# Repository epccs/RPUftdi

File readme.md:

# RPUusb

From <https://github.com/epccs/RPUusb>

## Overview

Alow a desktop or other host with USB to interface with [Gravimetric] that have an R-Pi header. It has two UARTs that can together operate the multi-drop serial. 

[Gravimetric]: https://github.com/epccs/Gravimetric

## Status

This board has a known problem with managers that lack power domains that allow one side to power down, that is to say if it has power and the application does not then the manager on the application board will be damaged. It is my hope that I can figure out how to use one of the new AVR-DB chips as a manager to fix this problem.

This is programmed with an in-circuit serial programming tool that is able to handle the 3.3V ATmega328pb target. I use an Arduino Uno with the [ArduinoISP] sketch and an SPI level shifter.

[ICSP]: https://github.com/epccs/Driver/tree/master/ICSP

[ArduinoISP]: https://github.com/arduino/Arduino/blob/master/build/shared/examples/11.ArduinoISP/ArduinoISP/ArduinoISP.ino

## [Hardware](./Hardware)

Hardware files and notes for referance.

## Example

TBD

## AVR toolchain

The core files for this board are in the /lib folder. Each example has its files and a Makefile in its own folder. The toolchain packages that I use are available on Ubuntu, Raspbian and Windows with WSL and Ubuntu installed. 

```
sudo apt-get install git make gcc-avr binutils-avr gdb-avr avr-libc avrdude
git clone https://github.com/epccs/RPUusb
```

* [gcc-avr](https://packages.ubuntu.com/search?keywords=gcc-avr)
* [binutils-avr](https://packages.ubuntu.com/search?keywords=binutils-avr)
* [gdb-avr](https://packages.ubuntu.com/search?keywords=gdb-avr)
* [avr-libc](https://packages.ubuntu.com/search?keywords=avr-libc)
* [avrdude](https://packages.ubuntu.com/search?keywords=avrdude)

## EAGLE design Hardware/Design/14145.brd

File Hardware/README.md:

# Hardware

## Overview

USB interface that plugs in place of an R-Pi. It plugs into an R-Pi header (e.g., [Gravimetric]). The CP2105 chip has two UARTs. The full-duplex multidrop bus is directly connected to the primary UART, while the secondary UART is connected to an MCU (ATmega328pb) that can act as a bridge for many of the R-Pi header pins (e.g., SPI, I2C) from the target board. A USB host can set the bootload address on the multi-drop serial with the I2C interface from the 328pb, and some other functions that an R-Pi has access to from the manager.

[Gravimetric]: https://github.com/epccs/Gravimetric

## Inputs/Outputs/Functions

* Full Duplex TX and RX from USB serial0 on R-Pi header pin 8 and 10.
* RTS and CTS from USB serial0 on R-Pi header pin 36 and 11.
* USB serial1 connects with an ATmega328pb for use with I2C/SPI.
* Fits RPUpi or Gravimetric.

## Uses

* Plugs in place of an R-Pi to allow USB from a computer to communicate with an RPU target.

# Table Of Contents

1. [Status](#status)
2. [Design](#design)
3. [Bill of Materials](#bill-of-materials)
4. [How To Use](#how-to-use)

# Status

```
        ^5  Done: Design (# = done), Layout, BOM, Review*, Order Boards, Assembly, Testing,
            WIP: Evaluation.
            Todo: 
            *during review the Design may change without changing the revision.
            High risk of damage to manager on application board, if manager has dual power domains that may fix
            # remove arduino headers
            # add header with 40 pin R-Pi pinout
            # swap MCU to ATmega328pb
            # swap ftdi with a dual UART port version Silabs CP2105
            # connect serial0 to RX/TX/nRTS/nCTS on R-Pi header
            # connect sierial1 to MCU's serial0
            # connect MCU's I2C0 to I2C on R-Pi header
            # connect MCU's I2C1 to the ID port on R-Pi header
            # connect MCU's SPI to SPI on R-Pi header
            # power with 3V3 from LDO and power the LDO from the USB header through the P-CH soft start. 

        ^4 Done: Design, Layout, BOM, Review*, Order Boards, Assembly, Testing, Evaluation.
           WIP: 
           Todo:  
           *during review the Design may change without changing the revision.
           location: 2017-3-17 Test Bench /w an OSEPP Uno R3

        ^3 location: 2016-10-1 Test Bench /w an OSEPP Uno R3, used to connect by CAT5 to outside parts and to bench parts as needed.
                     2017-1-5 ICP1 hacked open.
                     2017-3-17 scraped
```

Debugging and fixing problems i.e. [Schooling](./Schooling/)

Setup and methods used for [Evaluation](./Evaluation/)

# Design

The board is 0.063 thick, FR4, two layer, 1 oz copper with ENIG (gold) finish.

## Mounting

```
        Plugs into the R-Pi header of a multi-drop serial board.
```

## Electrical Schematic

## Testing

Check correct assembly and function with [Testing](./Testing/)

# Bill of Materials

The BOM is a CVS file, import it into a spreadsheet program like LibreOffice Calc (or Excel), or use a text editor.

Option | BOM's included
----- | ----- 
A. | [BRD] 
M. | [BRD] [SMD] [HDR] 

[BRD]: ./Design/14145BRD,BOM.csv
[SMD]: ./Design/14145SMD,BOM.csv
[HDR]: ./Design/14145HDR,BOM.csv

[Order Form](https://rpubus.org/Order_Form.html)

# How To Use

TDD

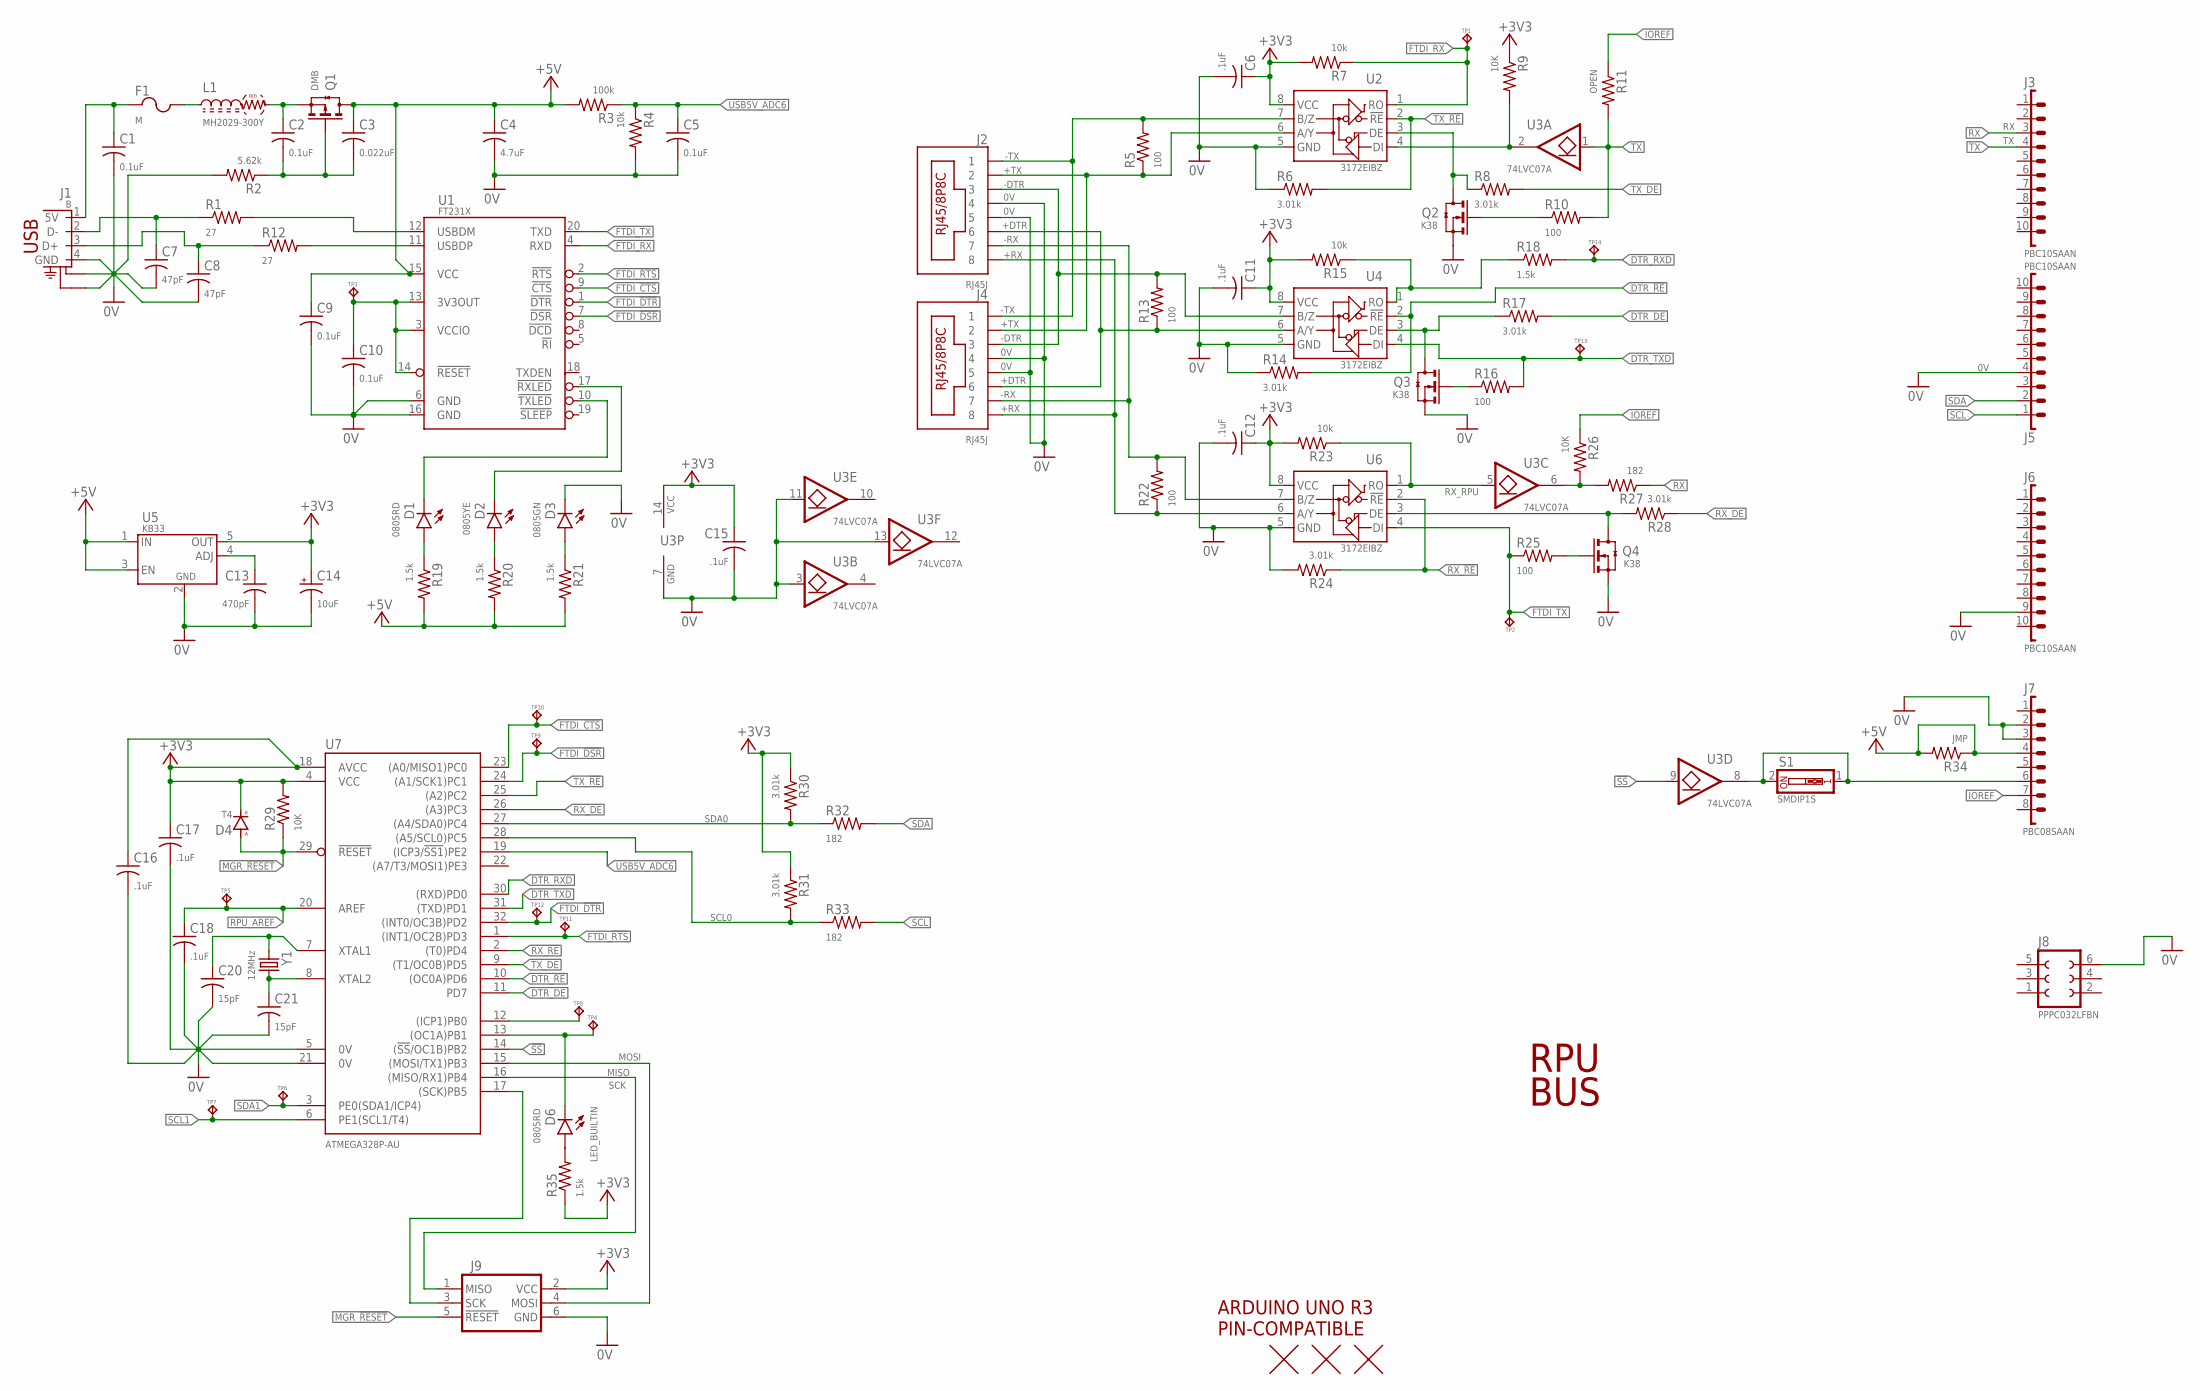
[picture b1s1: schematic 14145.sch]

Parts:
C1, C2, C5, C9, C10: 0.1uF; C0603(1608)
C3: 0.022uF; C0603(1608)
C4: 4.7uF; C1206(3216)
C6, C11, C12, C15, C16, C17, C18: .1uF; C0603(1608)
C7, C8: 47pF; C0603(1608)
C13: 470pF; C0603(1608)
C14: 10uF; 3216
C20, C21: 15pF; C0603(1608)
D1, D6: 0805RD; C0805(2012)
D2: 0805YE; C0805(2012)
D3: 0805GN; C0805(2012)
D4: T4; SOD123
F1: M; C1210(3225)
J1: B; USB-B-PTH
J2, J4: RJ45J; RJ45-8HZT
J3, J5, J6: PBC10SAAN; 1X10
J7: PBC08SAAN; 1X8
J8: PPPC032LFBN; F2X3
J9: ISP-SPIPTH; ISP
L1: MH2029-300Y; C0805(2012)
Q1: DMB; SOT23
Q2, Q3, Q4: K38; SOT23
R1, R12: 27; C0805(2012)
R2: 5.62k; C0805(2012)
R3: 100k; C0805(2012)
R4, R7, R15, R23: 10k; C0805(2012)
R5, R10, R13, R16, R22, R25: 100; C0805(2012)
R6, R8, R14, R17, R24, R28, R30, R31: 3.01k; C0805(2012)
R9, R26, R29: 10K; C0805(2012)
R11: OPEN; C0805(2012)
R18, R19, R20, R21, R35: 1.5k; C0805(2012)
R27, R32, R33: 182; C0805(2012)
R34: JMP; C0805(2012)
S1: SMDIP1S; SMD-DIPSWITCH-1
TP1, TP2, TP3, TP4, TP5, TP6, TP7, TP8, TP9, TP10, TP11, TP12, TP13, TP14: TPPAD1-08; P1-08
U1: FT231X; 20SSOP
U2, U4, U6: 3172EIBZ; SOIC8
U3: 74LVC07A; 14SOIC
U5: KB33; SOT23-5,SOT25
U7: ATMEGA328P-AU; TQFP32-08
U$1: ARDUINO-UNO; ARDUINO_UNO
U$2, U$3, U$4: FIDUCIAL1.27; FIDUCIAL-1.27
Y1: 12MHz; CSM-3X

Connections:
0V: C1.2, C4.2, C5.2, C6.2, C7.2, C8.2, C9.2, C10.2, C11.2, C12.2, C13.2, C14.-, C15.2, C16.2, C17.2, C18.2, C20.2, C21.2, D3.K, J1.4 (GND), J1.S1 (CHASSIS1), J1.S2 (CHASSIS2), J2.4, J2.5, J4.4, J4.5, J5.4, J6.9, J7.2, J7.3, J8.6, J9.6 (GND), Q2.2(S) (S), Q3.2(S) (S), Q4.2(S) (S), R2.2, R4.2, R6.1, R14.1, R24.2, U1.6 (GND), U1.16 (GND), U2.5 (GND), U3.3 (I), U3.7 (GND), U3.11 (I), U3.13 (I), U4.5 (GND), U5.2 (GND), U6.5 (GND), U7.5 (0V), U7.21 (0V)
!SS!: U3.9 (I), U7.14 ((!SS!/OC1B)PB2)
+3V3: C6.1, C11.1, C12.1, C14.+, C15.1, C16.1, C17.1, D4.C (K), J9.2 (VCC), R7.2, R9.1, R15.2, R23.2, R29.2, R30.1, R31.1, R35.1, U2.8 (VCC), U3.14 (VCC), U4.8 (VCC), U5.5 (OUT), U6.8 (VCC), U7.4 (VCC), U7.18 (AVCC)
+5V: C3.1, C4.1, C9.1, J7.4, Q1.3(D) (D), R3.2, R19.2, R20.2, R21.2, R34.1, R34.2, U1.15 (VCC), U5.1 (IN), U5.3 (EN)
+DTR: J2.6, J4.6, R13.1, U4.6 (A/Y)
+RX: J2.8, J4.8, R22.1, U6.6 (A/Y)
+TX: J2.2, J4.2, R5.1, U2.6 (A/Y)
-DTR: J2.3, J4.3, R13.2, U4.7 (B/Z)
-RX: J2.7, J4.7, R22.2, U6.7 (B/Z)
-TX: J2.1, J4.1, R5.2, U2.7 (B/Z)
D+: C8.1, J1.3 (D+), R12.1
D-: C7.1, J1.2 (D-), R1.1
DTR_!RE: R14.2, U4.2 (!RE), U7.10 ((OC0A)PD6)
DTR_DE: R17.2, U7.11 (PD7)
DTR_RXD: R18.2, TP14.TP, U7.30 ((RXD)PD0)
DTR_TXD: R16.2, TP13.TP, U4.4 (DI), U7.31 ((TXD)PD1)
FT3V3: C10.1, TP3.TP, U1.3 (VCCIO), U1.13 (3V3OUT), U1.14 (!RESET!)
FTDI_!CTS: TP10.TP, U1.9 (!CTS!), U7.23 ((A0/MISO1)PC0)
FTDI_!DSR: TP9.TP, U1.7 (!DSR!), U7.24 ((A1/SCK1)PC1)
FTDI_!DTR: TP12.TP, U1.1 (!DTR!), U7.32 ((INT0/OC3B)PD2)
FTDI_!RTS: TP11.TP, U1.2 (!RTS!), U7.1 ((INT1/OC2B)PD3)
FTDI_RX: R7.1, TP1.TP, U1.4 (RXD), U2.1 (RO)
FTDI_TX: R25.1, TP2.TP, U1.20 (TXD), U6.4 (DI)
IOREF: J7.7, R11.1, R26.1
LED_BUILTIN: D6.K, TP4.TP, U7.13 ((OC1A)PB1)
MGR_!RESET: D4.A, J9.5 (!RESET), R29.1, U7.29 (!RESET)
MISO: J9.1 (MISO), U7.16 ((MISO/RX1)PB4)
MOSI: J9.4 (MOSI), U7.15 ((MOSI/TX1)PB3)
unnamed: TP8.TP, U7.12 ((ICP1)PB0)
unnamed: J7.6, S1.1, S1.2, U3.8 (O)
unnamed: C1.1, F1.1, J1.1 (5V)
unnamed: F1.2, L1.1
unnamed: D2.A, R20.1
unnamed: D1.K, U1.10 (!TXLED)
unnamed: D2.K, U1.17 (!RXLED)
unnamed: R26.2, R27.2, U3.6 (O)
unnamed: Q4.3(D) (D), R28.2, U6.3 (DE)
unnamed: R1.2, U1.12 (USBDM)
unnamed: R12.2, U1.11 (USBDP)
unnamed: D3.A, R21.1
unnamed: Q2.1(G) (G), R10.1
unnamed: D1.A, R19.1
unnamed: Q2.3(D) (D), R8.1, U2.3 (DE)
unnamed: R15.1, R18.1, U4.1 (RO)
unnamed: Q3.3(D) (D), R17.1, U4.3 (DE)
unnamed: Q3.1(G) (G), R16.1
unnamed: C13.1, U5.4 (ADJ)
unnamed: Q4.1(G) (G), R25.2
unnamed: C2.1, L1.2, Q1.2(S) (S)
unnamed: C2.2, C3.2, Q1.1(G) (G), R2.1
unnamed: D6.A, R35.2
RPU_AREF: C18.1, TP5.TP, U7.20 (AREF)
RX: J3.3, R27.1
RX_!RE: R24.1, U6.2 (!RE), U7.2 ((T0)PD4)
RX_DE: R28.1, U7.26 ((A3)PC3)
RX_RPU: R23.1, U3.5 (I), U6.1 (RO)
SCK: J9.3 (SCK), U7.17 ((SCK)PB5)
SCL: J5.1, R33.2
SCL0: R31.2, R33.1, U7.28 ((A5/SCL0)PC5)
SCL1: TP7.TP, U7.6 (PE1(SCL1/T4))
SDA: J5.2, R32.2
SDA0: R30.2, R32.1, U7.27 ((A4/SDA0)PC4)
SDA1: TP6.TP, U7.3 (PE0(SDA1/ICP4))
TX: J3.4, R10.2, R11.2, U3.1 (I)
TX_!RE: R6.2, U2.2 (!RE), U7.25 ((A2)PC2)
TX_DE: R8.2, U7.9 ((T1/OC0B)PD5)
TX_RPU: R9.2, U2.4 (DI), U3.2 (O)
USB5V_ADC6: C5.1, R3.1, R4.1, U7.19 ((ICP3/!SS1!)PE2)
XTAL1: C20.1, U7.7 (XTAL1), Y1.1
XTAL2: C21.1, U7.8 (XTAL2), Y1.2

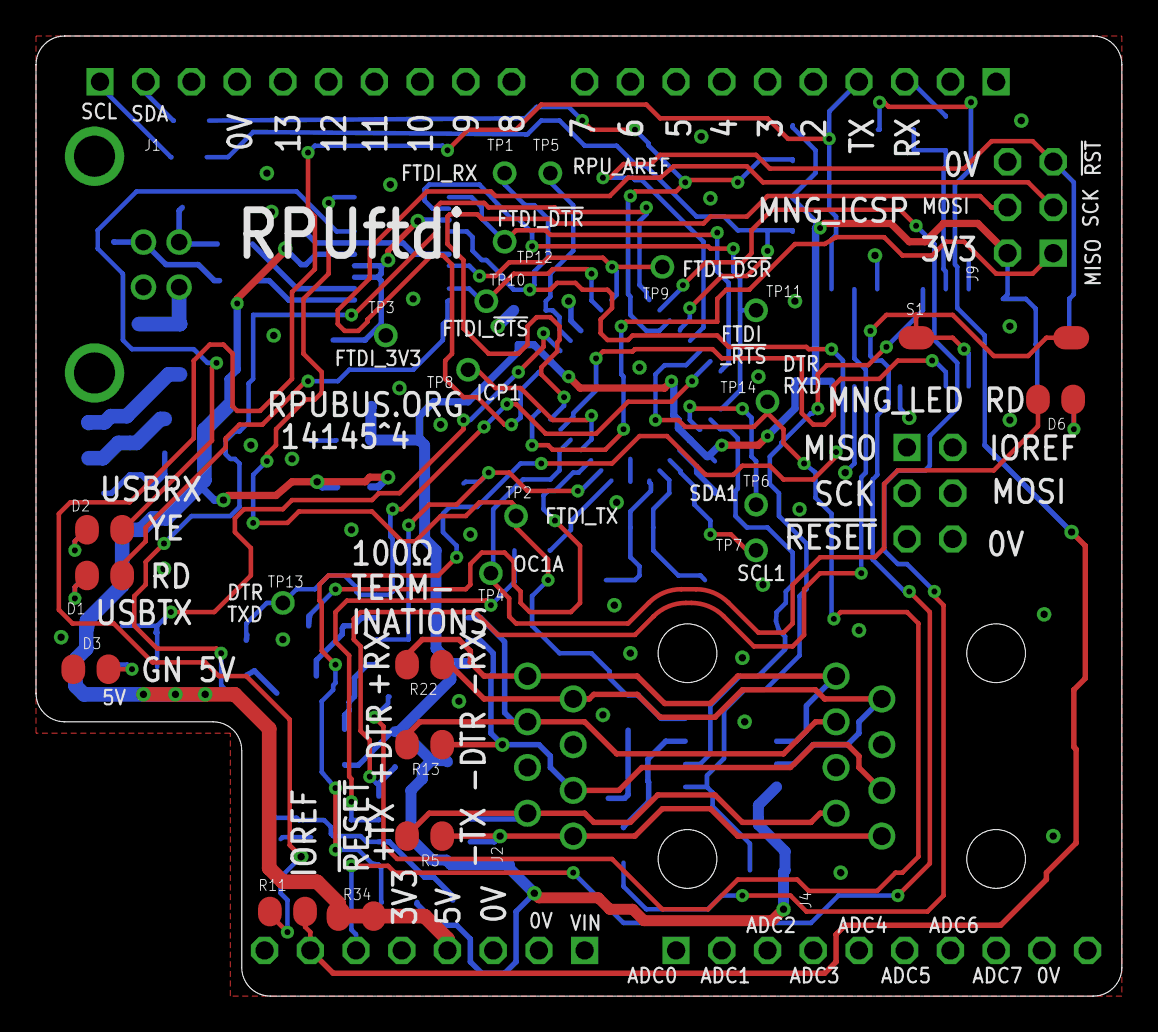
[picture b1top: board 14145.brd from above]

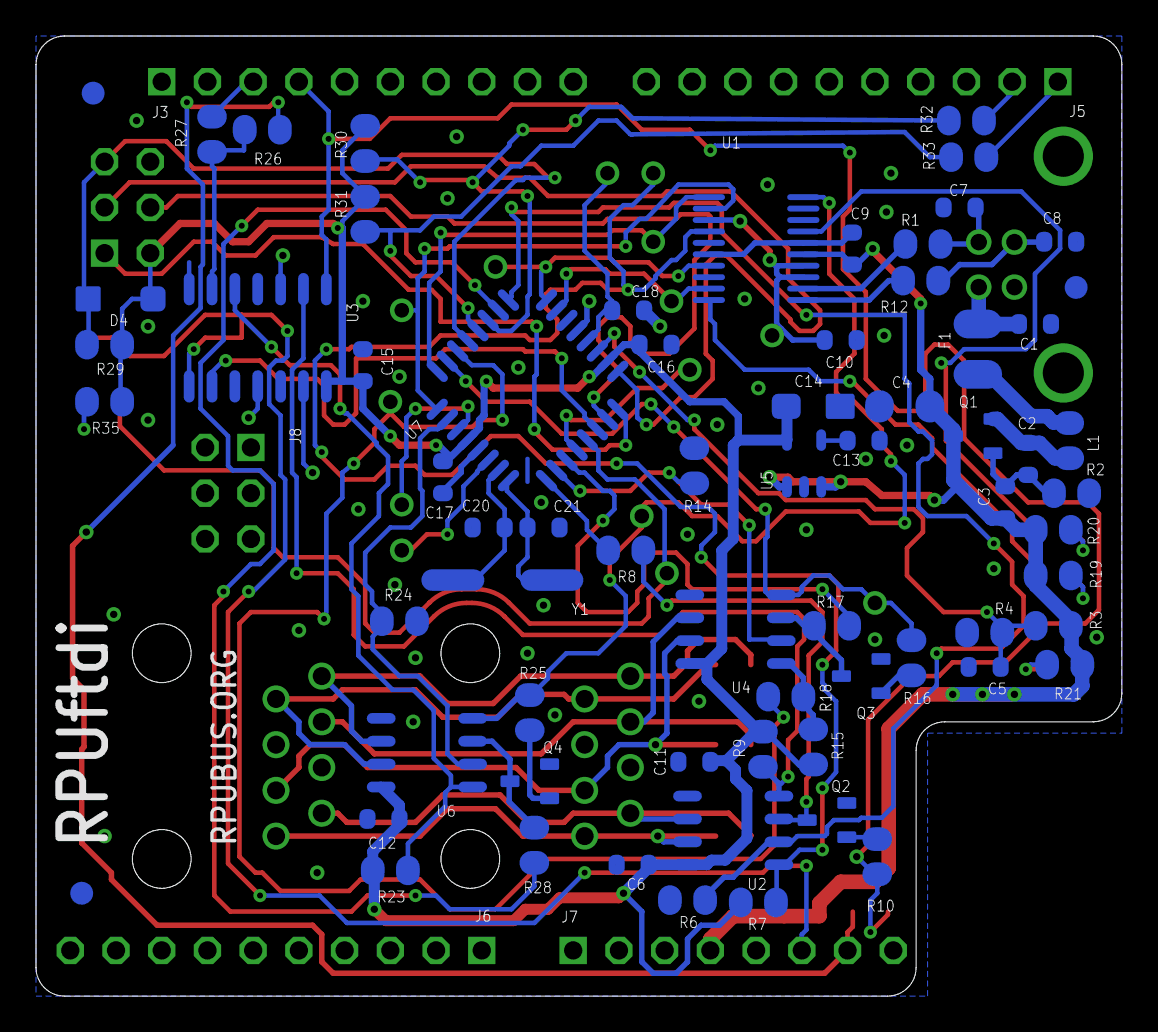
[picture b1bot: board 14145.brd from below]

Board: 2 copper layers, 60.3 x 53.3 mm, 102 parts (73 on the bottom side), 70 nets.

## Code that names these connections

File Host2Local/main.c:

/* Host2Local is for ATMega328 bus manager on RPUftdi board
 This program is free software; you can redistribute it and/or
modify it under the terms of the GNU General Public License
as published by the Free Software Foundation; either version 2
of the License, or (at your option) any later version.

This program is distributed in the hope that it will be useful,
but WITHOUT ANY WARRANTY; without even the implied warranty of
MERCHANTABILITY or FITNESS FOR A PARTICULAR PURPOSE.  See the
GNU General Public License for more details.

For a copy of the GNU General Public License use
http://www.gnu.org/licenses/gpl-2.0.html
 */ 

#include <util/delay.h>
#include <avr/io.h>
#include "../lib/timers.h"
#include "../lib/pin_num.h"
#include "../lib/pins_board.h"

#define BLINK_DELAY 500

static unsigned long blink_started_at;

int main(void)
{
    pinMode(LED_BUILTIN, OUTPUT);
    digitalWrite(LED_BUILTIN, HIGH);
    pinMode(FTDI_nRTS, INPUT);
    pinMode(FTDI_nCTS, OUTPUT);
    digitalWrite(FTDI_nCTS, LOW);
    pinMode(FTDI_nDTR, INPUT);
    pinMode(FTDI_nDSR, OUTPUT);
    digitalWrite(FTDI_nDSR, LOW);
    pinMode(RX_DE, OUTPUT);
    digitalWrite(RX_DE, HIGH); // allow RX pair driver to enable if FTDI_TX is low
    pinMode(TX_DE, OUTPUT);
    digitalWrite(TX_DE, HIGH); // allow TX pair driver to enable if TX (from MCU) is low
    pinMode(DTR_nRE, OUTPUT);
    digitalWrite(DTR_nRE, HIGH); // disable DTR pair receiver
    pinMode(DTR_DE, OUTPUT);
    digitalWrite(DTR_DE, LOW); // disable DTR pair driver
    pinMode(DTR_TXD, OUTPUT);
    digitalWrite(DTR_TXD, HIGH); // set DTR_TX true, which is default for serial.
    pinMode(nSS, OUTPUT); // nSS is input to a Open collector buffer used to pull to MCU nRESET low
    digitalWrite(nSS, HIGH); 
    
    uint8_t activate_bootloader = 0;
    
    initTimers(); //Timer0 Fast PWM mode, Timer1 & Timer2 Phase Correct PWM mode.

    sei(); // Enable global interrupts to start TIMER0

    blink_started_at = millis();
    
    while (1) 
    {
        unsigned long kRuntime = 0;
        
        kRuntime = millis() - blink_started_at;
        
        if ( (kRuntime > BLINK_DELAY) & activate_bootloader)
        {
            digitalToggle(LED_BUILTIN);
            
            // next toggle 
            blink_started_at += BLINK_DELAY; 
        }
        
        if ( !digitalRead(FTDI_nDTR) )  // both FTDI_nDTR and FTDI_nRTS are set (active low) when avrdude tries to use the bootloader
        { 
            if (!activate_bootloader)
            {
                activate_bootloader =1;
                digitalWrite(nSS, LOW);   // nSS goes through a open collector buffer to nRESET
                _delay_ms(20);  // hold reset low for a short time 
                digitalWrite(nSS, HIGH); // this will release the buffer with open colllector on MCU nRESET.
            }
        }
        else
        {
            activate_bootloader =0;
            digitalWrite(LED_BUILTIN, HIGH);
        }
    }    
}

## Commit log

2016-07-12 :neckbeard: Added .gitattributes
2016-07-12 init
    from http://epccs.org/hg/open/RPUftdi/
2016-08-27 BlinkLED: toggle has expected behavior now
2016-08-28 CheckDTR: used for board testing
2016-09-03 TwiSlave and Host2Local: for ^3
2016-09-04 Host2Remote: for ^3 send a byte from UART on DTR
    pair rather than toggling line
2016-09-06 Host2Remote: split into functions
    add TWI, and document some ideas to try
    add lockout and uart check to round robin
2016-09-06 Host2Remote: do not lockout host on ftdi only the local mcu
2016-09-07 Host2Remote: add I2C commands 2,3, and 5
2016-09-10 Host2Remote: sorting out issues
    add more feedback in the form of blinking lights
2016-09-11 Host2Remote: updates from mercurial repo
    lockout everything if host is foreign but only mcu if host is local
    disconnect when DTR pair has byte > 0x7F, start idea of a bus error
    char is like an int8_t on AVR but I thunked with uint8_t
    need improved host_is_foreign logic this is borken
2016-09-28 Host2Remote: work on logic
2016-09-29 Host2Remote: broadcast normal mode if localhost_active
2016-11-16 Hardware: add schematic
2016-11-18 Host2Remote: don't connect mcu if not rpu aware
2017-01-02 Host2Remote: broadcast after I2C read of rpu_addr /w bootloader_started
2017-01-02 Host2Remote: save rpu_bus address to eeprom
2017-01-05 Host2Remote: add host shutdown using ICP1
    and move some files from hg repo
2017-01-08 Host2Remote: don't blink when told to halt
2017-01-12 ardware: convert test and evaluation html to markdown
    from epccs/boards
2017-01-14 Hardware: baudrate tool
2017-01-15 Hardware: ^4 review
2017-01-24 Hardware: arrange parts and their references
2017-01-24 Hardware: bom update, price is based on my order qty
2017-01-24 example is a little more refined
2017-01-26 Hardware: example
2017-03-02 Hardware: ^4 assembly
2017-03-10 Hardware: ^4 testing
2017-03-26 Hardware: use 12MHz crystal, populate r5,r13,r22
2017-03-27 add link to tindie
2017-04-02 Hardware: ^4 evaluation remote reset
2017-04-04 one line apt-get packages
2017-04-19 Tindie link, status icon
2017-05-22 Host2Remote: sync with Remote, use makefile to config
2017-05-23 Hardware: crystal capacitors, eagle is not for open hardware
2017-05-26 Host2Remote: add lockout to status and rename rxBuffer as i2cBuffer
2017-05-26 Hardware: match node names on schmatic with firmware
2017-05-26 Hardware: node names are used as macro names and must be C identifiers
2017-10-01 Host2Remote: i2c command notes
2017-11-28 Hardware: update multidrop example
2018-07-13 https avrdude flags
2019-08-30 Hardware: ^5 layout remove arduino headers and add r-pi like interface
2019-08-30 Hardware: ^5 bom done, rdy for review
2019-09-28 Hardware: ^5 boards in hand
2020-07-31 RPUusb replaces RPUftid in readme
2020-08-21 Hardware: ^5 assy done test started
2020-08-22 Hardware: ^5 test wip, vscode, bootloader, m328pb atpack files, bsd files
2020-08-22 remove serial bus manager files, that function is on application boards
2020-08-22 BlinkLED: working uart & twi, schematic nodes and io_enum match
2020-08-23 i2c-debug: twi0 and twi1, and smoke, manager on gravimetric damaged
2020-08-29 Hardware: pin names on schematic match io_enum
2020-08-30 BCM24cntl: bcm24 pin used with PiUPDI to select uart or updi
2020-09-27 i2c-debug: setup to test i2c on the MacGyver, make rule to cp hdr for VSCode
2020-10-15 UPDImode: was BCM24cntl but BCM23 added for uart mode
2020-10-16 i2c-debug: init mode pins
2021-05-13 UPDImode: get all of bootmsg from the 328pb

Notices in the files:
parts and their libraries:
P-DCDC: Copyright (C) 2013 Ronald Steven Sutherland
under the terms of the GNU Free Documentation License, Version 1.2 or
any later version published by the Free Software Foundation; with no
C-C: Released under the Creative Commons
Attribution Share-Alike 3.0 License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
